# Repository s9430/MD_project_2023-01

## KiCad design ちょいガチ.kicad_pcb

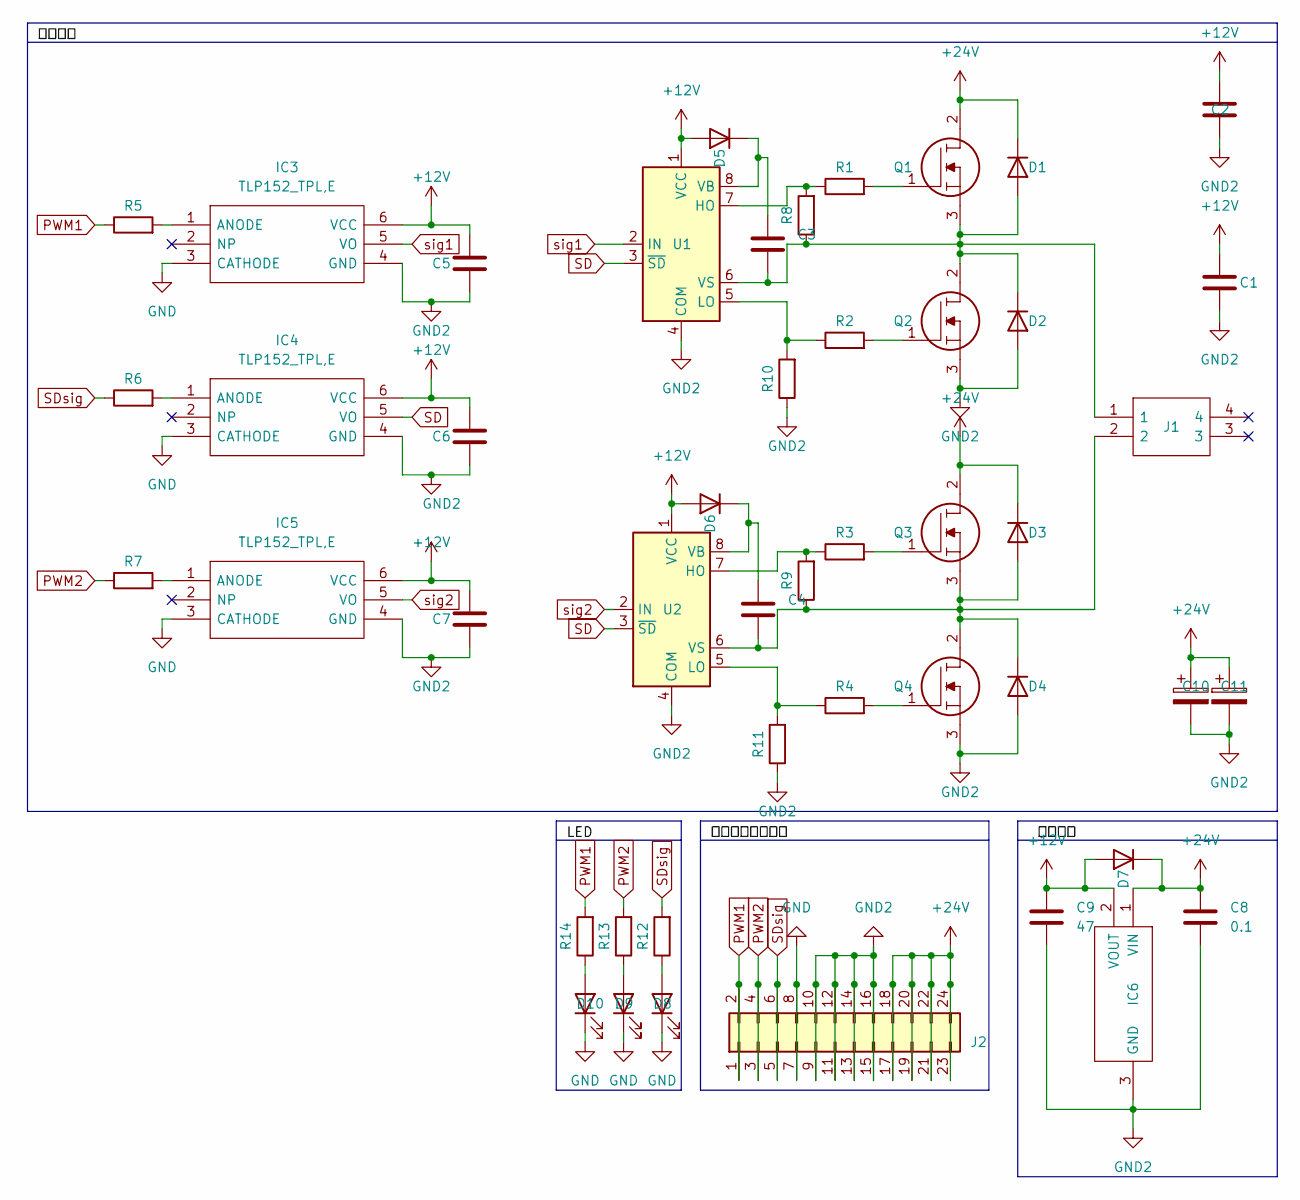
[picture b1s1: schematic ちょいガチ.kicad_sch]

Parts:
C1, C2, C3, C4: 10; C_1206_3216Metric
C5, C6, C7, C8: 0.1; C_0603_1608Metric
C9: 47; CP_Elec_6.3x7.7
C10, C11: 220; C_Elec_10x10.2
D1, D2, D3, D4, D5, D6, D7: 1N4001; D_0603_1608Metric
D8: SDsig; LED_0603_1608Metric
D9: PWM2; LED_0603_1608Metric
D10: PWM1; LED_0603_1608Metric
IC3, IC4, IC5: TLP152_TPL,E; SOIC127P700X230-6N; Manufacturer_Part_Number TLP152(TPL,E
IC6: NJM7800S-DL1; TO-252-3-L1; Manufacturer_Part_Number NJM7800S-DL1
J1: XT60PW-M; XT60PWM; Manufacturer_Part_Number XT60PW-M
J2: Conn_02x12_Odd_Even; PinHeader_2x12_P2.54mm_Horizontal
Q1, Q2, Q3, Q4: RSJ400N06FRATL; R6024KNJTL; Mouser Part Number 755-RSJ400N06FRATL
R1, R2: 10; R_0603_1608Metric
R3, R4, R9: R; R_0603_1608Metric
R5, R6, R7: 1k; R_0603_1608Metric
R8, R10, R11: 10k; R_0603_1608Metric
R12, R13, R14: 100; R_0603_1608Metric
U1, U2: IR2302; SOIC127P600X175-8N

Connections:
+12V: C1.1, C2.1, C5.1, C6.1, C7.1, C9.1, D5.2 (A), D6.2 (A), D7.2 (A), IC3.6 (VCC), IC4.6 (VCC), IC5.6 (VCC), IC6.2 (VOUT), U1.1 (VCC), U2.1 (VCC)
+24V: C8.1, C10.1, C11.1, D1.1 (K), D3.1 (K), D7.1 (K), IC6.1 (VIN), J2.17, J2.18, J2.19, J2.20, J2.21, J2.22, J2.23, J2.24, Q1.2, Q3.2
GND: D8.1 (K), D9.1 (K), D10.1 (K), IC3.3 (CATHODE), IC4.3 (CATHODE), IC5.3 (CATHODE), J2.7, J2.8
GND2: C1.2, C2.2, C5.2, C6.2, C7.2, C8.2, C9.2, C10.2, C11.2, D2.2 (A), D4.2 (A), IC3.4 (GND), IC4.4 (GND), IC5.4 (GND), IC6.3 (GND), J2.9, J2.10, J2.11, J2.12, J2.13, J2.14, J2.15, J2.16, Q2.3, Q4.3, R10.1, R11.1, U1.4 (COM), U2.4 (COM)
unnamed: C3.1, D5.1 (K), U1.8 (VB)
unnamed: C3.2, D1.2 (A), D2.1 (K), J1.1, Q1.3, Q2.2, R8.1, U1.6 (VS)
unnamed: C4.1, D6.1 (K), U2.8 (VB)
unnamed: C4.2, D3.2 (A), D4.1 (K), J1.2, Q3.3, Q4.2, R9.1, U2.6 (VS)
unnamed: D8.2 (A), R12.1
unnamed: D9.2 (A), R13.1
unnamed: D10.2 (A), R14.1
unnamed: IC3.1 (ANODE), R5.2
unnamed: IC4.1 (ANODE), R6.2
unnamed: IC5.1 (ANODE), R7.2
unnamed: Q1.1, R1.2
unnamed: Q2.1, R2.2
unnamed: Q3.1, R3.2
unnamed: Q4.1, R4.2
unnamed: R1.1, R8.2, U1.7 (HO)
unnamed: R3.1, R9.2, U2.7 (HO)
unnamed: R2.1, R10.2, U1.5 (LO)
unnamed: R4.1, R11.2, U2.5 (LO)
PWM1: J2.1, J2.2, R5.1, R14.2
PWM2: J2.3, J2.4, R7.1, R13.2
SD: IC4.5 (VO), U1.3 (~SD), U2.3 (~SD)
SDsig: J2.5, J2.6, R6.1, R12.2
sig1: IC3.5 (VO), U1.2 (IN)
sig2: IC5.5 (VO), U2.2 (IN)

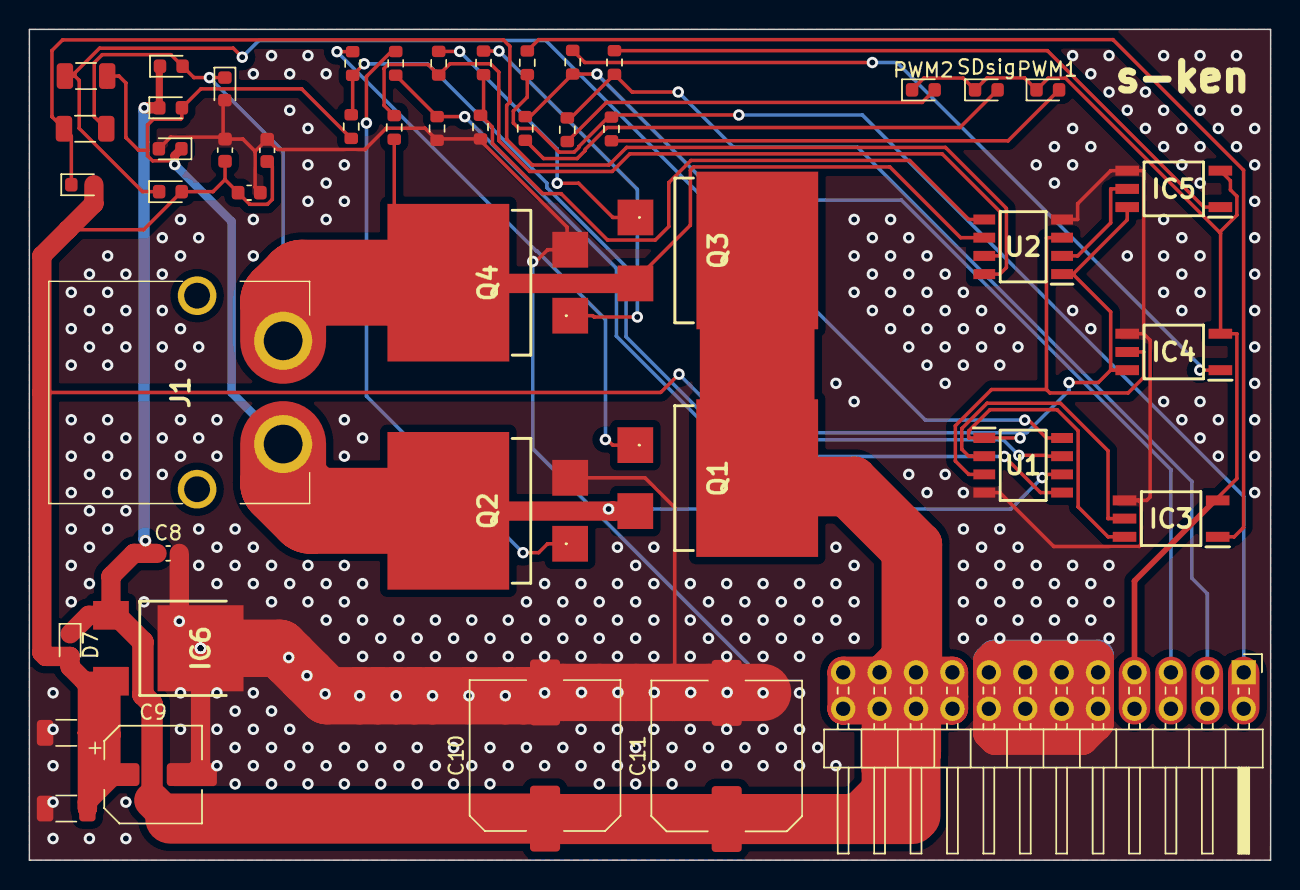
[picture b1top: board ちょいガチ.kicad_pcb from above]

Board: 2 copper layers, 86.6 x 58.0 mm, 47 parts (0 on the bottom side), 28 nets.
